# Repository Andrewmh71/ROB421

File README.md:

# Project Overview: Mirror Master

## Table of Contents

- [Introduction](#introduction)
- [Reasoning](#reasoning)
- [Beginning steps](#initial_test_videos)
- [End Result](#Completed_Videos)
- [Features & Artifacts](#features)
  - [Miguel Gaspar Garcia's Artifacts](#Miguel-Garcia's-Artifacts)
  - [Andrew Dillon's Artifacts](#Andrew-Dillon's-Artifacts)
  - [Connor's Rosenberger And Andrew Hiser's Artifacts ](#Conor-Rosenberger's-and-Andrew-Hiser's-Artifacts)
  - [Daniel McVay's Artifacts](#Daniel-McVay's-Artifacts)
- [Installation](#installation)
- [Configuration](#configuration)
- [API Reference](#api-reference)

# Introduction
- Project Mirror Master is a project designed, and created by Andrew Dillon, Andrew Hiser, Miguel Garcia Garspa, Daniel McVay, and Conor Rosenberger, who are currently students at Oregon State University in the Applied Robotics class (ROB 421), that would take a completely assembled and functioning Social Animated Mechanical Interlocutor (aka SAMI) robot currently used at oregon state for research, and would allow the user to install some modifications and a camera to allow the robot to be able to mirror the movements that would be performed right in front of it
- This repository contains all relevant documentation and visual images needed to transform the SAMI robot into Project: Mirror Master

## Reasoning:
- We decided on attempting this project as we had already added a camera to our SAMI Robot and thought that it would be difficult and interesting to attempt to have the robot copy movements, which none of us hav ever done before. With our goal to get it to copy in 2, or even 3 dimensions. However our final Project: Mirror Master is only able to function in a 2 dimensional space.

## initial_test_videos
- [Add Initial video showing finished robot and movement]
- https://oregonstateuniversity-my.sharepoint.com/:v:/r/personal/rosencon_oregonstate_edu/Documents/Attachments/PXL_20250609_202339570.mp4?csf=1&web=1&e=T4nsdH&nav=eyJwbGF5YmFja09wdGlvbnMiOnt9LCJyZWZlcnJhbEluZm8iOnsicmVmZXJyYWxBcHAiOiJTdHJlYW1XZWJBcHAiLCJyZWZlcnJhbE1vZGUiOiJtaXMiLCJyZWZlcnJhbFZpZXciOiJwb3N0cm9sbC1jb3B5bGluayIsInJlZmVycmFsUGxheWJhY2tTZXNzaW9uSWQiOiI1NTdmMjE0YS04M2RjLTQwODEtYmFhNi04MGIxMzBiOTg1NDcifX0%3D
- https://oregonstateuniversity-my.sharepoint.com/:v:/r/personal/rosencon_oregonstate_edu/Documents/Attachments/PXL_20250609_204853102.mp4?csf=1&web=1&e=03c3HS&nav=eyJwbGF5YmFja09wdGlvbnMiOnt9LCJyZWZlcnJhbEluZm8iOnsicmVmZXJyYWxBcHAiOiJTdHJlYW1XZWJBcHAiLCJyZWZlcnJhbE1vZGUiOiJtaXMiLCJyZWZlcnJhbFZpZXciOiJwb3N0cm9sbC1jb3B5bGluayIsInJlZmVycmFsUGxheWJhY2tTZXNzaW9uSWQiOiIzMjUwMjlkNy0zODQ1LTQxMDUtOTFkNi02ZWE5YjUxZGUyMjIifX0%3D
- https://oregonstateuniversity-my.sharepoint.com/:v:/r/personal/rosencon_oregonstate_edu/Documents/Attachments/PXL_20250609_201514187.mp4?csf=1&web=1&e=xjAquG&nav=eyJwbGF5YmFja09wdGlvbnMiOnt9LCJyZWZlcnJhbEluZm8iOnsicmVmZXJyYWxBcHAiOiJTdHJlYW1XZWJBcHAiLCJyZWZlcnJhbE1vZGUiOiJtaXMiLCJyZWZlcnJhbFZpZXciOiJwb3N0cm9sbC1jb3B5bGluayIsInJlZmVycmFsUGxheWJhY2tTZXNzaW9uSWQiOiJjOTcwYmIyZi03MjZjLTRmZjQtOTBlNS1iY2I4MGQ1MTM2ZjAifX0%3D
- https://oregonstateuniversity-my.sharepoint.com/:v:/r/personal/rosencon_oregonstate_edu/Documents/Attachments/PXL_20250609_201230615.mp4?csf=1&web=1&e=I6WGn8&nav=eyJwbGF5YmFja09wdGlvbnMiOnt9LCJyZWZlcnJhbEluZm8iOnsicmVmZXJyYWxBcHAiOiJTdHJlYW1XZWJBcHAiLCJyZWZlcnJhbE1vZGUiOiJtaXMiLCJyZWZlcnJhbFZpZXciOiJwb3N0cm9sbC1jb3B5bGluayIsInJlZmVycmFsUGxheWJhY2tTZXNzaW9uSWQiOiI3NDNlYzgyNC00OTBlLTQ1ZDAtODNhMC05NDIwMDAxMzI5NGYifX0%3D
- https://oregonstateuniversity-my.sharepoint.com/:v:/r/personal/rosencon_oregonstate_edu/Documents/Attachments/PXL_20250609_203106960.mp4?csf=1&web=1&e=AGnGCI&nav=eyJwbGF5YmFja09wdGlvbnMiOnt9LCJyZWZlcnJhbEluZm8iOnsicmVmZXJyYWxBcHAiOiJTdHJlYW1XZWJBcHAiLCJyZWZlcnJhbE1vZGUiOiJtaXMiLCJyZWZlcnJhbFZpZXciOiJwb3N0cm9sbC1jb3B5bGluayIsInJlZmVycmFsUGxheWJhY2tTZXNzaW9uSWQiOiJhODQwMWE3MS1jODI4LTQ1MTItOWQ1MS0wMjNhZjQ0ZTE0MTEifX0%3D

## Completed_Videos
- https://oregonstateuniversity-my.sharepoint.com/:v:/r/personal/rosencon_oregonstate_edu/Documents/Attachments/PXL_20250609_205245309.mp4?csf=1&web=1&e=FG9Jtm&nav=eyJwbGF5YmFja09wdGlvbnMiOnt9LCJyZWZlcnJhbEluZm8iOnsicmVmZXJyYWxBcHAiOiJTdHJlYW1XZWJBcHAiLCJyZWZlcnJhbE1vZGUiOiJtaXMiLCJyZWZlcnJhbFZpZXciOiJwb3N0cm9sbC1jb3B5bGluayIsInJlZmVycmFsUGxheWJhY2tTZXNzaW9uSWQiOiIxNTYzYzQwNS1hMzljLTQ2MmYtOTc1MC0yMmQ1NzYyM2E5ZmQifX0%3D
- https://oregonstateuniversity-my.sharepoint.com/:v:/r/personal/rosencon_oregonstate_edu/Documents/Attachments/PXL_20250609_202801648.mp4?csf=1&web=1&e=P8FL6E&nav=eyJwbGF5YmFja09wdGlvbnMiOnt9LCJyZWZlcnJhbEluZm8iOnsicmVmZXJyYWxBcHAiOiJTdHJlYW1XZWJBcHAiLCJyZWZlcnJhbE1vZGUiOiJtaXMiLCJyZWZlcnJhbFZpZXciOiJwb3N0cm9sbC1jb3B5bGluayIsInJlZmVycmFsUGxheWJhY2tTZXNzaW9uSWQiOiI4ODNhM2MwMy1mYjRlLTQyM2QtYjBjNi01M2Q0MmYyY2EwY2MifX0%3D
- https://oregonstateuniversity-my.sharepoint.com/:v:/r/personal/rosencon_oregonstate_edu/Documents/Attachments/PXL_20250609_204949665.mp4?csf=1&web=1&e=HbA6Ku&nav=eyJwbGF5YmFja09wdGlvbnMiOnt9LCJyZWZlcnJhbEluZm8iOnsicmVmZXJyYWxBcHAiOiJTdHJlYW1XZWJBcHAiLCJyZWZlcnJhbE1vZGUiOiJtaXMiLCJyZWZlcnJhbFZpZXciOiJwb3N0cm9sbC1jb3B5bGluayIsInJlZmVycmFsUGxheWJhY2tTZXNzaW9uSWQiOiJjYzYxMGFiYS02MTUxLTQ2ODQtOTA2NS02NjY1YWUxZDE2YzcifX0%3D
- https://oregonstateuniversity-my.sharepoint.com/:v:/r/personal/rosencon_oregonstate_edu/Documents/Attachments/PXL_20250609_202513612.mp4?csf=1&web=1&e=4geajd&nav=eyJwbGF5YmFja09wdGlvbnMiOnt9LCJyZWZlcnJhbEluZm8iOnsicmVmZXJyYWxBcHAiOiJTdHJlYW1XZWJBcHAiLCJyZWZlcnJhbE1vZGUiOiJtaXMiLCJyZWZlcnJhbFZpZXciOiJwb3N0cm9sbC1jb3B5bGluayIsInJlZmVycmFsUGxheWJhY2tTZXNzaW9uSWQiOiJlMTRhMzQ3Yy00NWY2LTRmYTktYWMyMy01NTI5OTRkMGUzNjkifX0%3D

# Features
## Supplemental Artifacts:
- Miguel Garcia's Artifacts
    -  Gimbal tracking of the head in order to track user if they step out of view

https://github.com/user-attachments/assets/5335354e-1cad-4e65-9cfb-70e90b637bce

- Andrew Dillon's Artifacts:
  - Focus of facial recognition aspects of the movement
  - Isolates single user and only mirrors that user:
  - Checks to see if it is an authorized user, only then it would copy movements
  - Would look register the emotion of the user and attempt to overwrite the current expression on the robot
  - [Zip files for working videos][Rob 421 Final Project Andrew Dillon Individual Artifacts (2).zip](https://github.com/user-attachments/files/20701953/Rob.421.Final.Project.Andrew.Dillon.Individual.Artifacts.2.zip)
  - [Rob 421 Final Project Andrew Dillon Individual Artifacts Part 2.zip](https://github.com/user-attachments/files/20701964/Rob.421.Final.Project.Andrew.Dillon.Individual.Artifacts.Part.2.zip)

- Conor Rosenberger's and Andrew Hiser's Artifacts:
  - Large Focus on 2D and later 3D Motion
  - Artifact 1) 2D skeleton pose estimation and collision detection and prevention
  - Artifact 2) Modified Json behavior file to allow robot to make "Show Sky" Gesture
  - Artifact 3) 3D pose matching and angle determination utilizing x, y, and z coordinates
  - Video of TEST 3D motion angle determination: https://github.com/user-attachments/assets/0f409fa8-7e65-4dfb-aff2-d3c45caf36b4
  - Designed a headshell to mask a Logitech 923E camera to soften the appearance of the robot and camera [camerashellfinalfinalfinalfinalfinal.zip](https://github.com/user-attachments/files/20702064/camerashellfinalfinalfinalfinalfinal.zip)
    
-Daniel McVay's Artifacts:
  - Create collision detection for system to determine if a motion is safe to mirror
  - Artifact 1) created code for identification of both shoulders and elbow to initialize system
  - Artifact 2) created code that simulates the arms position and checks for the collision {image below}

  - Artifact 3) Collision detection checks individually for left arm and right arm individually
NOTES: Overall the code woorks to test and simulate positions using the Trimesh library, however, because we could not get 3d detection to work,
       it would have been a waist time to try to implement that with minor affect, Instead we bound motions to prevent collisions.

## General Robot Facts
- Using 1/2 cameras to pose match and copy shown movement in all 3 coordinate directions when compared to the standard 2 directions
- Use DeepFace Facial recognition to isolate and recognize authorized users and copy the movements of only those authorized users
- MediaPipe to capture the skeleton pose matching
- Calculates servo angles based off the skeleton to match the targets movements and send them to the robot for it to replicate
- Utilizes up to 21 servos to replicate human joints and allow the robot to replicate human motion

# Installation
Assemble Logitech c920e camera and combine it with the camera cover and assemble it on top of the robot

## Captions/Speakers/Video/Microphone
- Current camera model for project is a Logitech c920e camera
- Currently uses hooked up computers speakers for sound and audio

### Configuration
-  3D tracking
-  Accurate Angle and servo determination
  - more human like bending of the arms, biceps and shoulders. It should not bend in non human ways when copying movement
-  Safe and reasonable servo movement
-  Collision prediction and prevention

# System Requirements
- Must be on Python ver. 3.11
  - one of the few versions that would work with mediapipe and DeepFace
- Python Module Version:
  - mediapipe: 0.10.21
  - numpy: 1.26.4
  - opencv: 4.11.0.86
  - DeepFace https://github.com/serengil/deepface

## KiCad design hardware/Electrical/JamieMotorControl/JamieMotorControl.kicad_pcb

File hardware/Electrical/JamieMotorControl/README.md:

# Motor control driver board
Driver board for the servo bus motors. Includes connection for LED eyes, serial control for bus servo motors, and power control for bus servo motors, with mounting spot for microcontroller dev board.

## To-Do Edits for Final PCB
 - Zane says we should round our pcb corners lol
 - Swap the data and ground pins on the jsts so the right angle jsts can actually be connected to the board on the same side as everything else, oops
 - Add a label for the transistors for the relay for the actual type of transistor
 - Update PCB revision on board when updating board

## Bill of Materials (BoM)
This BoM includes all items necessary to populate this particular PCB. It does not include all items necessary for the entire robot, which can be found [here](../../BoM.md). The parts listed are standalone items you need, as well as a consolidated list of all items you can purchase as a group from [DigiKey](https://www.digikey.com/). 

 - 1x [Mini Arduino ATMEGA2560](https://www.amazon.com/dp/B0D7ZT5M2R), any manufacturer who matches this footprint/pinout will work.
 - 1x [AMASS XT60PW-M Connector](https://www.tme.com/us/en-us/details/xt60pw-m/dc-power-connectors/amass/)
 - 1x [AMASS XT30PW-M Connector](https://www.tme.com/us/en-us/details/xt30pw-m/dc-power-connectors/amass/)
 - 2.54mm pitch female header strips, for connecting the Arduino
 - [DigiKey Part List](../JamieMotorControlBoardDigiKey.csv)

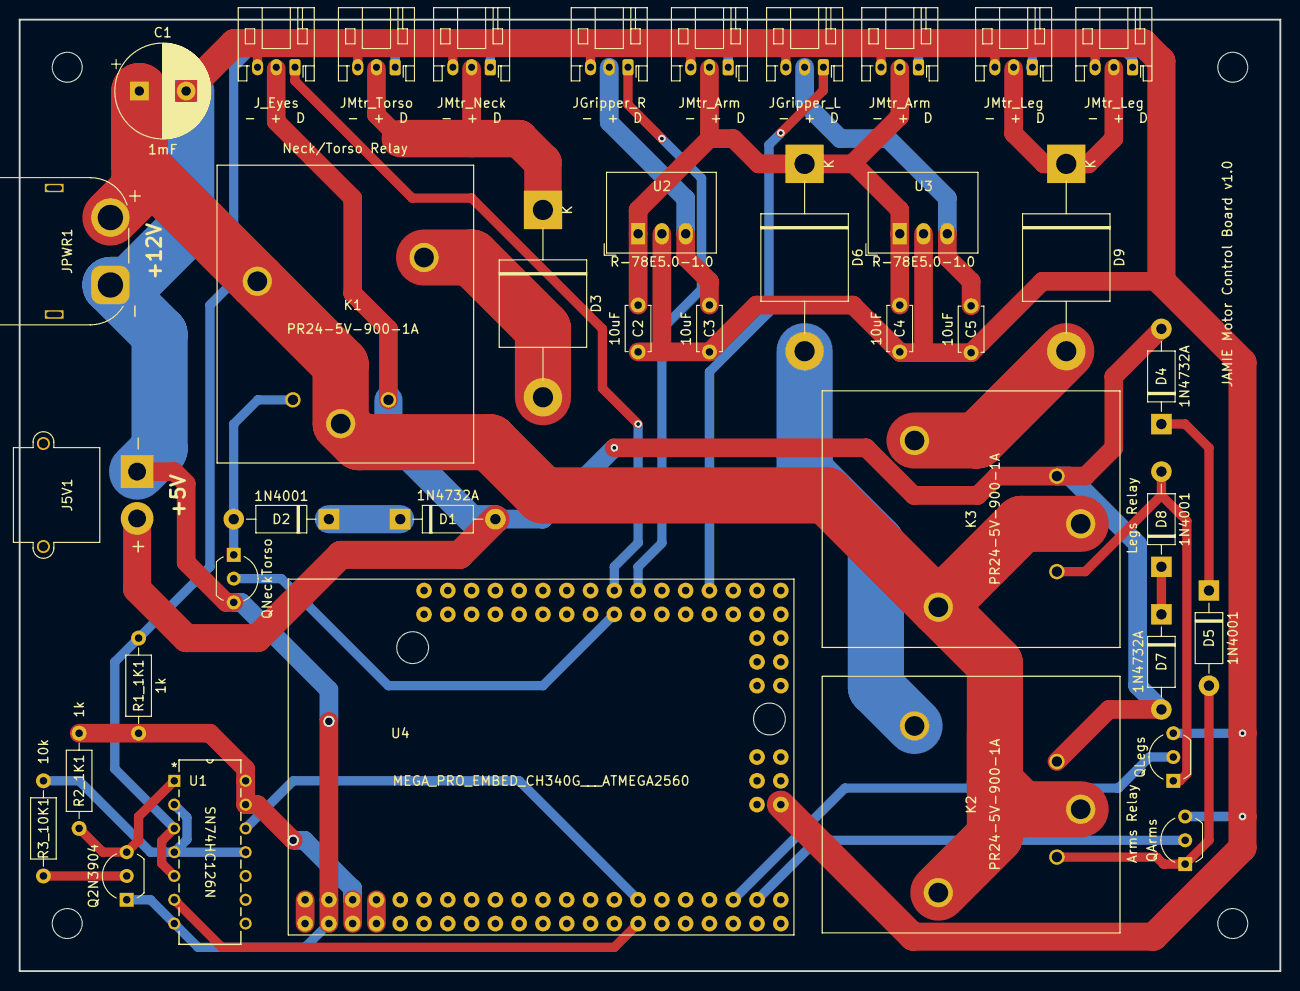
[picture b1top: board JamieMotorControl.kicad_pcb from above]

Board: 2 copper layers, 134.6 x 101.6 mm, 43 parts (0 on the bottom side), 32 nets.

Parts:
C1: 1mF; CP_Radial_D10.0mm_P5.00mm
C2, C3, C4, C5: 10uF; C_Disc_D4.7mm_W2.5mm_P5.00mm
D1, D4, D7: 1N4732A; D_DO-41_SOD81_P10.16mm_Horizontal
D2, D5, D8: 1N4001; D_DO-41_SOD81_P10.16mm_Horizontal
D3, D6, D9: 40SQ045; D_P600_R-7_P20.00mm_Horizontal
H1, H2, H3, H4: MountingHole; MountingHole_3.2mm_M3
J5V1: Conn_01x02; AMASS_XT30PW-M_1x02_P2.50mm_Horizontal
JGripper_L: JST01x03_R; JST_PH_S3B-PH-K_1x03_P2.00mm_Horizontal
JGripper_R: JST01x03_R; JST_PH_S3B-PH-K_1x03_P2.00mm_Horizontal
JMtr_Arm: JST01x03_R; JST_PH_S3B-PH-K_1x03_P2.00mm_Horizontal
JMtr_Arm#2: JST01x03_R; JST_PH_S3B-PH-K_1x03_P2.00mm_Horizontal
JMtr_Leg: JST01x03_R; JST_PH_S3B-PH-K_1x03_P2.00mm_Horizontal
JMtr_Leg#2: JST01x03_R; JST_PH_S3B-PH-K_1x03_P2.00mm_Horizontal
JMtr_Neck: JST01x03_R; JST_PH_S3B-PH-K_1x03_P2.00mm_Horizontal
JMtr_Torso: JST01x03_R; JST_PH_S3B-PH-K_1x03_P2.00mm_Horizontal
JPWR1: Conn_01x02; AMASS_XT60PW-M_1x02_P7.20mm_Horizontal
J_Eyes: JST01x03_R; JST_PH_S3B-PH-K_1x03_P2.00mm_Horizontal
K1, K2, K3: PR24-5V-900-1A; RELAY_PR24-5V-900-1A
Q2N3904: 2N3904; TO-92_Inline_Wide
QArms: BC337; TO-92_Inline_Wide
QLegs: BC337; TO-92_Inline_Wide
QNeckTorso: BC337; TO-92_Inline_Wide
R1_1K1, R2_1K1: 1k; R_Axial_DIN0207_L6.3mm_D2.5mm_P10.16mm_Horizontal
R3_10K1: 10k; R_Axial_DIN0207_L6.3mm_D2.5mm_P10.16mm_Horizontal
U1: SN74HC126N; N14
U2, U3: R-78E5.0-1.0; Converter_DCDC_RECOM_R-78E-0.5_THT
U4: MEGA_PRO_EMBED_CH340G___ATMEGA2560; MODULE_MEGA_PRO_EMBED_CH340G___ATMEGA2560

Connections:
5V: D1.2 (A), D4.2 (A), D7.2 (A), J5V1.2, J_Eyes.2, K1.A1, K2.A1, K3.A1
12V: C1.1, JPWR1.2, K1.COM_1, K1.COM_2, K2.COM_1, K2.COM_2, K3.COM_1, K3.COM_2
/MTR_SIG: JMtr_Arm.1, JMtr_Arm#2.1, JMtr_Leg.1, JMtr_Leg#2.1, JMtr_Neck.1, JMtr_Torso.1, R1_1K1.2, U1.3 (1Y), U1.5 (2A)
/TX_EN: Q2N3904.3 (C), R2_1K1.2, U1.1 (1OE)
/TX_O: R3_10K1.1, U1.2 (1A), U1.4 (2OE), U1.11 (4Y)
ArmsRelay: QArms.2 (B), U4.D28
Eyes: J_Eyes.1, U4.D32
GND: C1.2, C2.2, C3.2, C4.2, C5.2, J5V1.1, JGripper_L.3, JGripper_R.3, JMtr_Arm.3, JMtr_Arm#2.3, JMtr_Leg.3, JMtr_Leg#2.3, JMtr_Neck.3, JMtr_Torso.3, JPWR1.1, J_Eyes.3, Q2N3904.1 (E), QArms.3 (E), QLegs.3 (E), QNeckTorso.3 (E), U1.7 (GND), U2.2 (GND), U3.2 (GND), U4.GND_1 (GND), U4.GND_2 (GND), U4.GND_3 (GND)
HeadTorsoRelay: QNeckTorso.2 (B), U4.D33
LGripper: JGripper_L.1, U4.D40
LegsRelay: QLegs.2 (B), U4.D26
unnamed: D1.1 (K), D2.1 (K)
unnamed: D2.2 (A), K1.A2, QNeckTorso.1 (C)
unnamed: D3.2 (A), K1.NO
unnamed: D3.1 (K), JMtr_Neck.2, JMtr_Torso.2
unnamed: D4.1 (K), D5.1 (K)
unnamed: D5.2 (A), K2.A2, QArms.1 (C)
unnamed: D6.2 (A), K2.NO
unnamed: C2.1, C4.1, D6.1 (K), JMtr_Arm.2, JMtr_Arm#2.2, U2.1 (IN), U3.1 (IN)
unnamed: D7.1 (K), D8.1 (K)
unnamed: D8.2 (A), K3.A2, QLegs.1 (C)
unnamed: D9.2 (A), K3.NO
unnamed: D9.1 (K), JMtr_Leg.2, JMtr_Leg#2.2
unnamed: C5.1, JGripper_L.2, U3.3 (OUT)
unnamed: C3.1, JGripper_R.2, U2.3 (OUT)
unnamed: Q2N3904.2 (B), R3_10K1.2
unnamed: U4.3V3_1 (3V3), U4.3V3_2 (3V3)
unnamed: U4.VIN_1 (VIN), U4.VIN_2 (VIN)
RGripper: JGripper_R.1, U4.D34
RX1: U1.6 (2Y), U4.D19
TX1: U1.12 (4A), U4.D18
VCC: R1_1K1.1, R2_1K1.1, U1.13 (4OE), U1.14 (VCC), U4.5V_1 (5V), U4.5V_2 (5V), U4.5V_3 (5V)

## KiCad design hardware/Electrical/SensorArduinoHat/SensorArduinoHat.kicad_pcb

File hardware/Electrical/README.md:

# Aaron Robot Electrical
All of the information for the electrical systems and wiring for the robot.

## Future Improvements
TODO:
 - So much assembly

## Cable Fabrication
There are three power cables that need to be assembled to supply power to the robot. The components and assembly instructions for each are provided below.

For the fork connectors we used [14-16 gauge, #8 fork connectors with heat shrink attached, from wirefy](https://www.amazon.com/dp/B07YBHDBST) and for the spade connectors, we used [10-12 guage, female quick disconnect spade connectors with heat shrink, also from wirefy](https://www.amazon.com/dp/B08BP57G94).

### 12V PCB to Power Supply
This cable assembly connects the 12V power on the motor control PCB to the 12V power supply for the robot.

#### Materials
 - 1x red 14AWG braided wire, 18" length minimum
 - 2x red heat shrink pieces
 - 1x black 14AWG braided wire, 18" length minimum
 - 2x black heat shrink pieces
 - 1x XT-60 female plug
 - 2x fork connector #8, 16-14 gauge opening

#### Assembly
For connecting the wires to the XT-60 connector, you may follow [this](https://www.youtube.com/watch?v=eeDYUymM3XI) short video tutorial.

### 5V PCB to Power Supply
This cable assembly connects the 5V power on the motor control PCB to the 5V power supply for the robot.

#### Materials
 - 1x red 18AWG braided wire, 24" length minimum
 - 2x red heat shrink pieces
 - 1x black 18AWG braided wire, 24" length minimum
 - 2x black heat shrink pieces
 - 1x XT-30 female plug
 - 2x fork connector #8, 22-16 gauge opening

#### Assembly

### 12V Power Supply to Outlet to 5V Power Supply
This cable assembly connects both the 12V power supply and 5V power supply to the power outlet on the back of the chair that takes 120VAC wall power. The 12V supply and 5V supply are at different locations and could use different cable lengths, but for ease of assembly, we use the same lengths of wire for both of them.

#### Materials
 - 2x red 14AWG braided wire, 12" length minimum
 - 3x red heat shrink pieces
 - 2x black 14AWG braided wire, 12" length minimum
 - 3x black heat shrink pieces
 - 2x yellow 14AWG braided wire, 12" length minimum
 - 3x yellow heat shrink pieces
 - 6x fork connector #8, 16-14 gauge opening
 - 3x female spade connector, 12-10 gauge opening

#### Assembly

### Hip Motor to Control PCB JST Cable
For the two motors in the hips, the JST cables that come with the motors will need to be lengthened to reach the motor pcb. You'll need to splice in a 12" length of wire. This can be done by soldering, or with mechanical splice connectors such as [these](https://www.amazon.com/dp/B0DGLJJRZ5).

You will need:
 - 1x 3 pin JST cable (comes with motor)
 - 1x 3 wire cable, 12" length minimum
 - Solder and heat shrink or [2x mechanical crimp splicers](https://www.amazon.com/dp/B0DGLJJRZ5).

Split the JST cable that comes with the motor down the middle. Then splice in the 12" length of cable, such that the connector ends match each other (*not* mirrored!) See the photo below.

### Eye Panel Short Cable
This is the short cable combining the two LED array panels for the eyes.

You will need:
 - 2x 3pin JST XH2.54 connectors
 - 1x 3 wire cable, 4" length (try not to go long)

Assemble the connectors to the cable such that the connectors match each other (*not* mirrored!). See the photo below.

### Eye Panel Long Cable
This is the logn cable connecting the first LED array panel to the motor control board. 

You will need:
 - 1x 3pin JST XH2.54 connector
 - 1x 3pin JST PH2.0 connector
 - 1x 3 wire cable, 16" length minimum

Assemble the cable so that wires connect into the connectors as shown in the image below.

### Gripper Cable
The cable to connector the gripper servo motors to the motor control pcb. It converts a dupont connector to a JST PH2.0.

You will need:
 - 1x 3pin JST PH2.0 connector
 - 1x 3pin Dupont female connector
 - 1x 3 wire cable, ?? length minimum

Connect the dupont to the jst as shown below, where white is the signal line, red is power, and black is ground. 

## Bill of Materials
Currently all in the excel doc one level up

 - Power Supply: 12V, 30A, buck converter down to 6V (Need to check current still)
 - PTC Fuses for each motor: RKEF075-2
 - Relays for each motor group: PR9-5V-200-1A
 - NPN Transistors for each motor group relay controller: BC547CBU-ND
 - Diode between motors and servo: 15SQ100

## Wiring Guide

## Custom PCBs

### Safety Circuitry

#### Motor Current Characteristics

See the motor current characteristics for the arms (without gripper) and legs below. The measured torso nod motor current during operation was seen as a maximum of 0.6A, and the stall current was measured at 1.12A. The measured torso tilt current during operation similarly hit a maximum of 0.6A, but the stall current when held still was 1.99A.

#### Safety Circuit Current Breakdown
We have PTC fuses to protect the servos from melting themselves, and 15A relays so we can cut power to the servos if operation is not currently necessary.

##### Relay Circuits
There are 6 relay groups, broken down for each arm, and leg, as well as the neck and torso. Each relay needs 40mA control current, which becomes 240mA current from the Arduino 5V line. To turn the control circuit on and off, each relay has an individual NPN transistor. These transistors are controlled by a common Arduino pin.

 - Arm Motors: Max Rating: 12.5A, 75W @ 6VDC
    - Chest Shoulder
    - Shoulder
    - Arm Twist
    - Elbow
    - Single Tendon Gripper
 - Leg Motors: Max Rating: 7.5A, 45W @ 6VDC
    - Hip
    - Knee
    - Ankle
    - Hip flexor motor? (add another 2.5A)
 - Head Motors: Max Rating: 7.5A, 45W @ 6VDC
    - Head Twist
    - Head Nod
    - Head Tilt
    - Camera pan motor? (add another 2.5A)
 - Torso Motors: Max Rating: ~6A, 45W @ 7.4VDC
    - Torso Tilt
    - Torso Bow
    - Spine-hip bow point? (adds another ~3A)

## References
 - [Flyback diode example circuit](https://blog.mbedded.ninja/electronics/components/relays/)

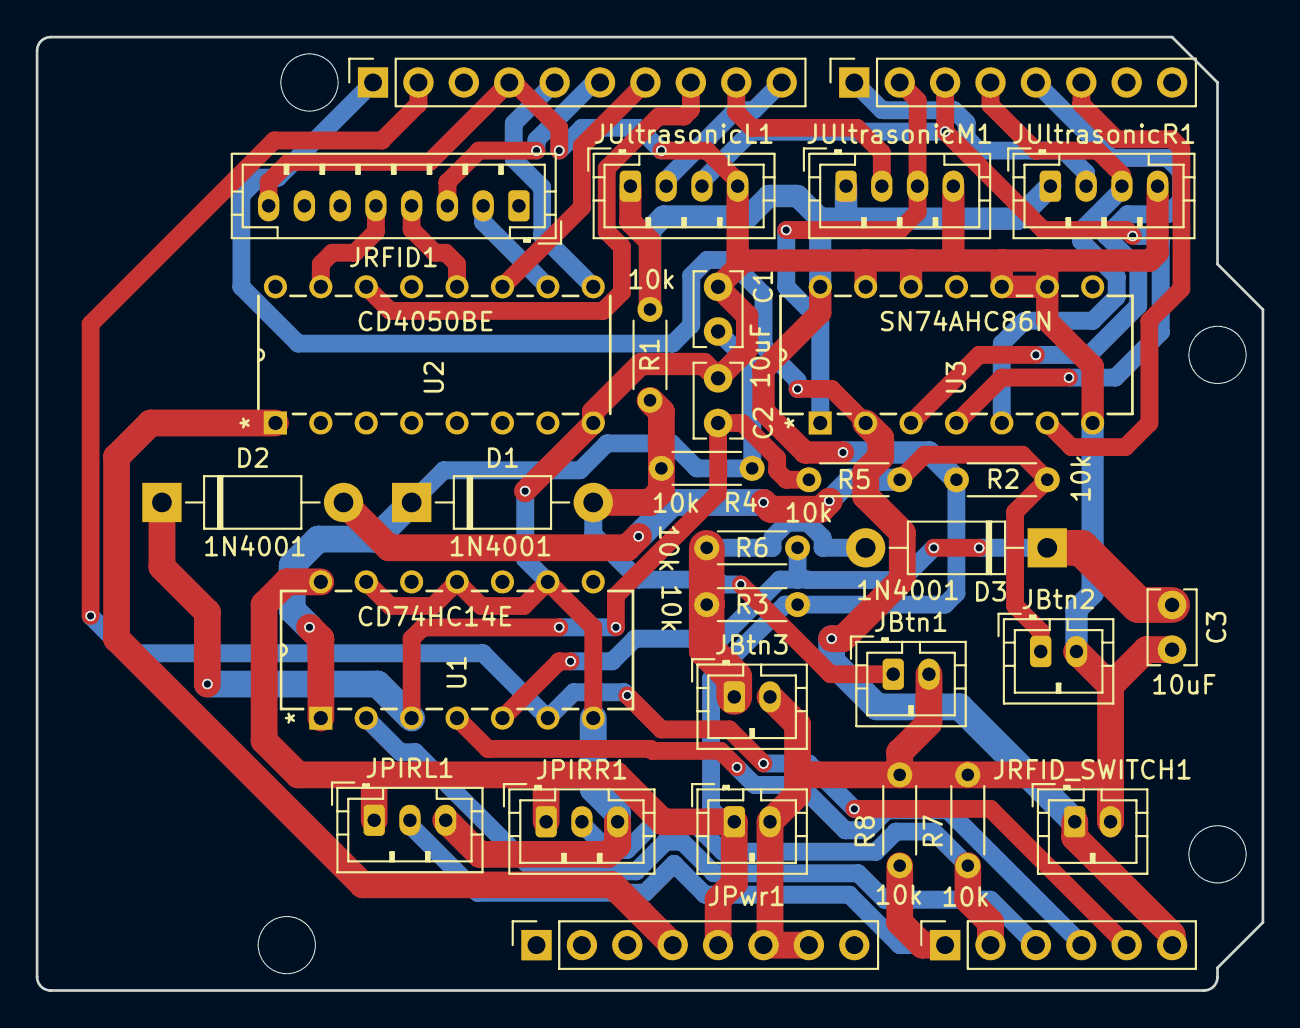
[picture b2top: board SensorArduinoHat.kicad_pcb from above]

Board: 2 copper layers, 68.6 x 53.3 mm, 36 parts (0 on the bottom side), 30 nets.

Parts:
C1, C2, C3: 10uF; C_Rect_L4.0mm_W2.5mm_P2.50mm
D1, D2, D3: 1N4001; D_DO-41_SOD81_P10.16mm_Horizontal
J1: Power; PinSocket_1x08_P2.54mm_Vertical
J2: Digital/PWM; PinSocket_1x10_P2.54mm_Vertical
J3: Analog; PinSocket_1x06_P2.54mm_Vertical
J4: Digital/PWM; PinSocket_1x08_P2.54mm_Vertical
JBtn1, JBtn2, JBtn3: Conn_01x02; JST_PH_B2B-PH-K_1x02_P2.00mm_Vertical
JPIRL1: Conn_01x03; JST_PH_B3B-PH-K_1x03_P2.00mm_Vertical
JPIRR1: Conn_01x03; JST_PH_B3B-PH-K_1x03_P2.00mm_Vertical
JPwr1: Conn_01x02; JST_PH_B2B-PH-K_1x02_P2.00mm_Vertical
JRFID1: Conn_01x08; JST_PH_B8B-PH-K_1x08_P2.00mm_Vertical
JRFID_SWITCH1: Conn_01x02; JST_PH_B2B-PH-K_1x02_P2.00mm_Vertical
JUltrasonicL1: Conn_01x04; JST_PH_B4B-PH-K_1x04_P2.00mm_Vertical
JUltrasonicM1: Conn_01x04; JST_PH_B4B-PH-K_1x04_P2.00mm_Vertical
JUltrasonicR1: Conn_01x04; JST_PH_B4B-PH-K_1x04_P2.00mm_Vertical
MH1, MH2, MH3, MH4: MountingHole_3.2mm
R1, R2, R3, R4, R5, R6, R7, R8: 10k; R_Axial_DIN0204_L3.6mm_D1.6mm_P5.08mm_Horizontal
U1: CD74HC14E; N14
U2: CD4050BE; N16
U3: SN74AHC86N; N14

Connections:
5V: J1.5, JPIRL1.1, JPIRR1.1, JPwr1.1, JUltrasonicL1.1, JUltrasonicM1.1, JUltrasonicR1.1, R1.1, R2.1, R3.1, U1.14 (VCC), U3.14 (VCC)
+3V3: J1.4, U2.1 (VCC)
/2: J4.6, U3.6 (2Y)
/4: J4.4, JUltrasonicR1.3, U3.5 (2B)
/7: J4.1, JUltrasonicR1.2
/8: J2.10, JUltrasonicL1.2
/12: J2.6, JRFID1.3
/13: J2.5, U2.9 (D)
/*3: J4.5, U3.3 (1Y)
/*5: J4.3, JUltrasonicL1.3, U3.4 (2A)
/*6: J4.2, JUltrasonicM1.3, U3.1 (1A)
/*9: J2.9, JUltrasonicM1.2
/*10: J2.8, U2.14 (F)
/*11: J2.7, U2.11 (E)
/A0: J3.1, JPIRL1.2, R8.1
/A1: J3.2, JPIRR1.2, R7.1
/A2: J3.3, U1.2 (1Y)
/A3: J3.4, U1.4 (2Y)
/BtnPin3: J2.2, J3.5, U1.6 (3Y)
/MOSI: JRFID1.4, U2.12 (K=E)
/RFID Card Trigger: J2.1, J3.6, JRFID_SWITCH1.1, U3.2 (1B)
/SCK: JRFID1.2, U2.10 (J=D)
/SSEL: JRFID1.5, U2.15 (L=F)
GND: C1.2, C2.2, C3.2, J1.6, J1.7, J2.4, JBtn1.2, JBtn2.2, JBtn3.2, JPIRL1.3, JPIRR1.3, JPwr1.2, JRFID1.8, JRFID_SWITCH1.2, JUltrasonicL1.4, JUltrasonicM1.4, JUltrasonicR1.4, R7.2, R8.2, U1.7 (GND), U1.9 (4A), U1.11 (5A), U1.13 (6A), U2.8 (VSS), U3.7 (GND), U3.9 (3A), U3.10 (3B), U3.12 (4A), U3.13 (4B)
unnamed: D1.2 (A), JBtn1.1, R1.2, R4.2
unnamed: C1.1, D1.1 (K), R4.1, U1.1 (1A)
unnamed: D2.2 (A), JBtn2.1, R2.2, R5.2
unnamed: C2.1, D2.1 (K), R5.1, U1.3 (2A)
unnamed: D3.2 (A), JBtn3.1, R3.2, R6.2
unnamed: C3.1, D3.1 (K), R6.1, U1.5 (3A)

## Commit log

2025-05-07 Initial commit of SAMI_ROBOT class repo
2025-05-07 Added Skelton Frame Code
2025-05-07 increased model accuracy
2025-05-07 New Frame ignores below shoulders
2025-05-09 Added Facial recognition to boot up process
    Note: Will need to add an authorised image of yourself called "authorized" in order for it to work
2025-05-09 Reference robot moving code
2025-05-09 Modified skeletor to map shoulder angles to servos
2025-05-13 Added hypothetical collison printout
2025-05-13 Added TeamDance.json to repository
2025-05-14 upadted joint home angles
2025-05-14 new Skeletor has elbows and shoulders
2025-05-14 Elbow and shoulder tracking
2025-05-14 Miguels head gimabal code
2025-05-27 Update README.md
    Started editing the README for the portfolio assignment
2025-05-28 Added face_tracker module and updated Skeletor for neck tracking integration
2025-05-28 Changed to GHUM task and added functions
2025-05-28 created collision code, need to fix wall locations and then fix code for links
2025-05-30 Update README.md
    Portfolio info
2025-05-30 Update README.md
    Added the module versions (maybe useful?)
2025-06-03 3D motion Code
2025-06-03 this code detects angle collisions for the right arm, inputs are chest, shoulder, bicep, and elbow angles. Outputs true, good motion, or false, which means to abort
2025-06-03 created left arm function, call left and right separetly
2025-06-04 Updated Skeletor
2025-06-04 Added task files
2025-06-04 This function should add the face tracking feature to our robot
2025-06-04 Added facial recognition and overwrites new emote
2025-06-04 Merged with main, modified Skeletor
2025-06-04 Modified skeletor
2025-06-04 Face tracking update
2025-06-04 Skeletor stuff
2025-06-06 Switched back to 2D (partial completion)
2025-06-09 Updated skeleton code
2025-06-09 Changes to skeletor
2025-06-10 Added Skeletor3D
2025-06-10 added commments to explain each section for future use. persnal number 541 891 6043
2025-06-10 Update README.md
    added my sections and photos
2025-06-12 Add files via upload
    Added Andrew Dillon's Modified behaviour jsons
2025-06-12 Rename Applaud.json to Andrew Dillon Modified Applaud.json
2025-06-12 Rename BowToUser.json to Andrew Dillon Modified BowToUser.json
2025-06-12 Rename ExpressYes.json to Andrew Dillon Modified ExpressYes.json
2025-06-13 Fixed typo
